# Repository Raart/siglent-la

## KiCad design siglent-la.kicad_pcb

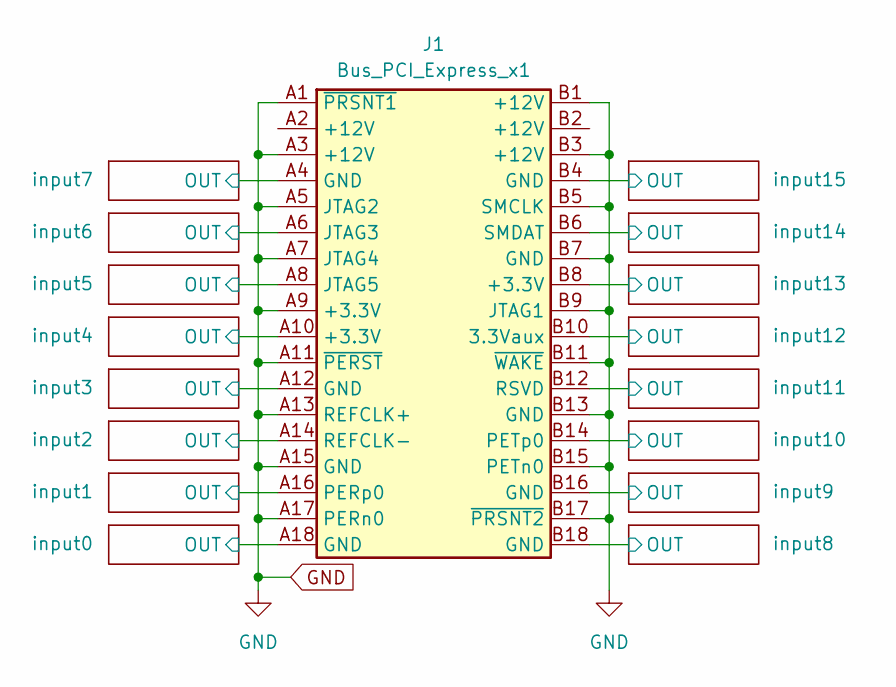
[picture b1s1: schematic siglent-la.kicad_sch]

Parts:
J1: Bus_PCI_Express_x1; BUS_PCIexpress_x1

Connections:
/input0/OUT: J1.A18 (GND); also elsewhere on the board
/input1/OUT: J1.A16 (PERp0); also elsewhere on the board
/input2/OUT: J1.A14 (REFCLK-); also elsewhere on the board
/input3/OUT: J1.A12 (GND); also elsewhere on the board
/input4/OUT: J1.A10 (+3.3V); also elsewhere on the board
/input5/OUT: J1.A8 (JTAG5); also elsewhere on the board
/input6/OUT: J1.A6 (JTAG3); also elsewhere on the board
/input7/OUT: J1.A4 (GND); also elsewhere on the board
/input8/OUT: J1.B18 (GND); also elsewhere on the board
/input9/OUT: J1.B16 (GND); also elsewhere on the board
/input10/OUT: J1.B14 (PETp0); also elsewhere on the board
/input11/OUT: J1.B12 (RSVD); also elsewhere on the board
/input12/OUT: J1.B10 (3.3Vaux); also elsewhere on the board
/input13/OUT: J1.B8 (+3.3V); also elsewhere on the board
/input14/OUT: J1.B6 (SMDAT); also elsewhere on the board
/input15/OUT: J1.B4 (GND); also elsewhere on the board
GND: J1.A1 (~PRSNT1), J1.A3 (+12V), J1.A5 (JTAG2), J1.A7 (JTAG4), J1.A9 (+3.3V), J1.A11 (~PERST), J1.A13 (REFCLK+), J1.A15 (GND), J1.A17 (PERn0), J1.B1 (+12V), J1.B3 (+12V), J1.B5 (SMCLK), J1.B7 (GND), J1.B9 (JTAG1), J1.B11 (~WAKE), J1.B13 (GND), J1.B15 (PETn0), J1.B17 (~PRSNT2); also elsewhere on the board

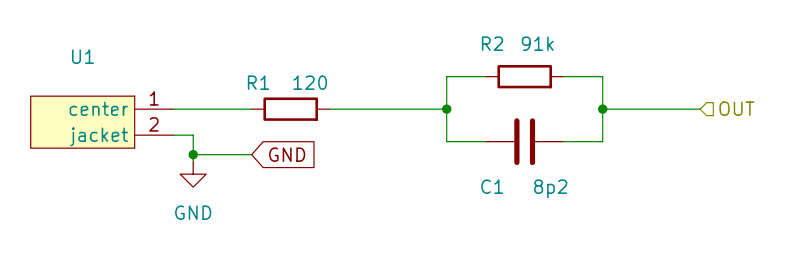
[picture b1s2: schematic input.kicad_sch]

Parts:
C1: 8p2; C_0603_1608Metric
R1: 120; R_0603_1608Metric
R2: 91k; R_0603_1608Metric
U1: solder_coax

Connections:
/input0/OUT: C1.2, R2.2; also elsewhere on the board
GND: U1.2 (jacket); also elsewhere on the board
unnamed: R1.1, U1.1 (center)
unnamed: C1.1, R1.2, R2.1

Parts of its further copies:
C2, C3, C4, C5, C6, C7, C8, C9, C10, C11, C12, C13, C14, C15, C16: 8p2; C_0603_1608Metric
R3, R5, R7, R9, R11, R13, R15, R17, R19, R21, R23, R25, R27, R29, R31: 120; R_0603_1608Metric
R4, R6, R8, R10, R12, R14, R16, R18, R20, R22, R24, R26, R28, R30, R32: 91k; R_0603_1608Metric
U2, U3, U4, U5, U6, U7, U8, U9, U10, U11, U12, U13, U14, U15, U16: solder_coax

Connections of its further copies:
/input1/OUT: C2.2, R4.2; also elsewhere on the board
/input2/OUT: C3.2, R6.2; also elsewhere on the board
/input3/OUT: C4.2, R8.2; also elsewhere on the board
/input4/OUT: C5.2, R10.2; also elsewhere on the board
/input5/OUT: C6.2, R12.2; also elsewhere on the board
/input6/OUT: C7.2, R14.2; also elsewhere on the board
/input7/OUT: C8.2, R16.2; also elsewhere on the board
/input8/OUT: C9.2, R18.2; also elsewhere on the board
/input9/OUT: C10.2, R20.2; also elsewhere on the board
/input10/OUT: C11.2, R22.2; also elsewhere on the board
/input11/OUT: C12.2, R24.2; also elsewhere on the board
/input12/OUT: C13.2, R26.2; also elsewhere on the board
/input13/OUT: C14.2, R28.2; also elsewhere on the board
/input14/OUT: C15.2, R30.2; also elsewhere on the board
/input15/OUT: C16.2, R32.2; also elsewhere on the board
GND: U2.2 (jacket), U3.2 (jacket), U4.2 (jacket), U5.2 (jacket), U6.2 (jacket), U7.2 (jacket), U8.2 (jacket), U9.2 (jacket), U10.2 (jacket), U11.2 (jacket), U12.2 (jacket), U13.2 (jacket), U14.2 (jacket), U15.2 (jacket), U16.2 (jacket); also elsewhere on the board
unnamed: C2.1, R3.2, R4.1
unnamed: C3.1, R5.2, R6.1
unnamed: C4.1, R7.2, R8.1
unnamed: C5.1, R9.2, R10.1
unnamed: C6.1, R11.2, R12.1
unnamed: C7.1, R13.2, R14.1
unnamed: C8.1, R15.2, R16.1
unnamed: C9.1, R17.2, R18.1
unnamed: C10.1, R19.2, R20.1
unnamed: C11.1, R21.2, R22.1
unnamed: C12.1, R23.2, R24.1
unnamed: C13.1, R25.2, R26.1
unnamed: C14.1, R27.2, R28.1
unnamed: C15.1, R29.2, R30.1
unnamed: C16.1, R31.2, R32.1
unnamed: R3.1, U2.1 (center)
unnamed: R5.1, U3.1 (center)
unnamed: R7.1, U4.1 (center)
unnamed: R9.1, U5.1 (center)
unnamed: R11.1, U6.1 (center)
unnamed: R13.1, U7.1 (center)
unnamed: R15.1, U8.1 (center)
unnamed: R17.1, U9.1 (center)
unnamed: R19.1, U10.1 (center)
unnamed: R21.1, U11.1 (center)
unnamed: R23.1, U12.1 (center)
unnamed: R25.1, U13.1 (center)
unnamed: R27.1, U14.1 (center)
unnamed: R29.1, U15.1 (center)
unnamed: R31.1, U16.1 (center)

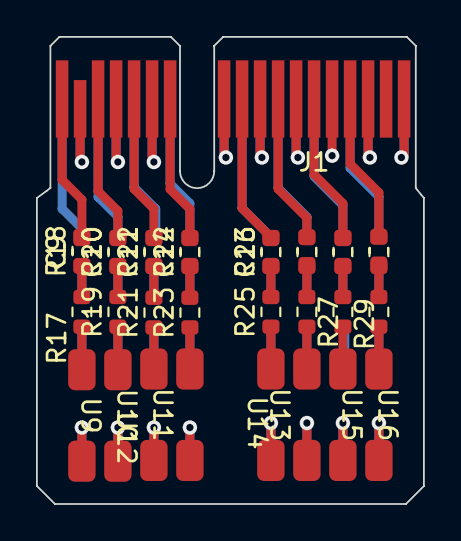
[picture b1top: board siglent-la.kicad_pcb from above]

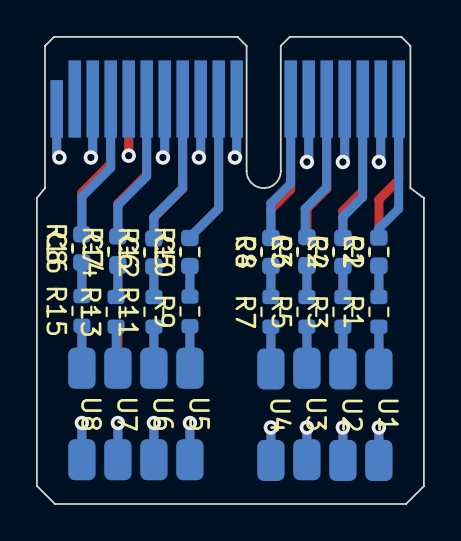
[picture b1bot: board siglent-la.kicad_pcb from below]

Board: 4 copper layers, 21.5 x 26.0 mm, 65 parts (32 on the bottom side), 49 nets.

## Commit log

2024-11-02 Update siglent-la.kicad_sch
    Connector specs are no more accessible on the original address.
    Can be downloaded from archive.org instead.
